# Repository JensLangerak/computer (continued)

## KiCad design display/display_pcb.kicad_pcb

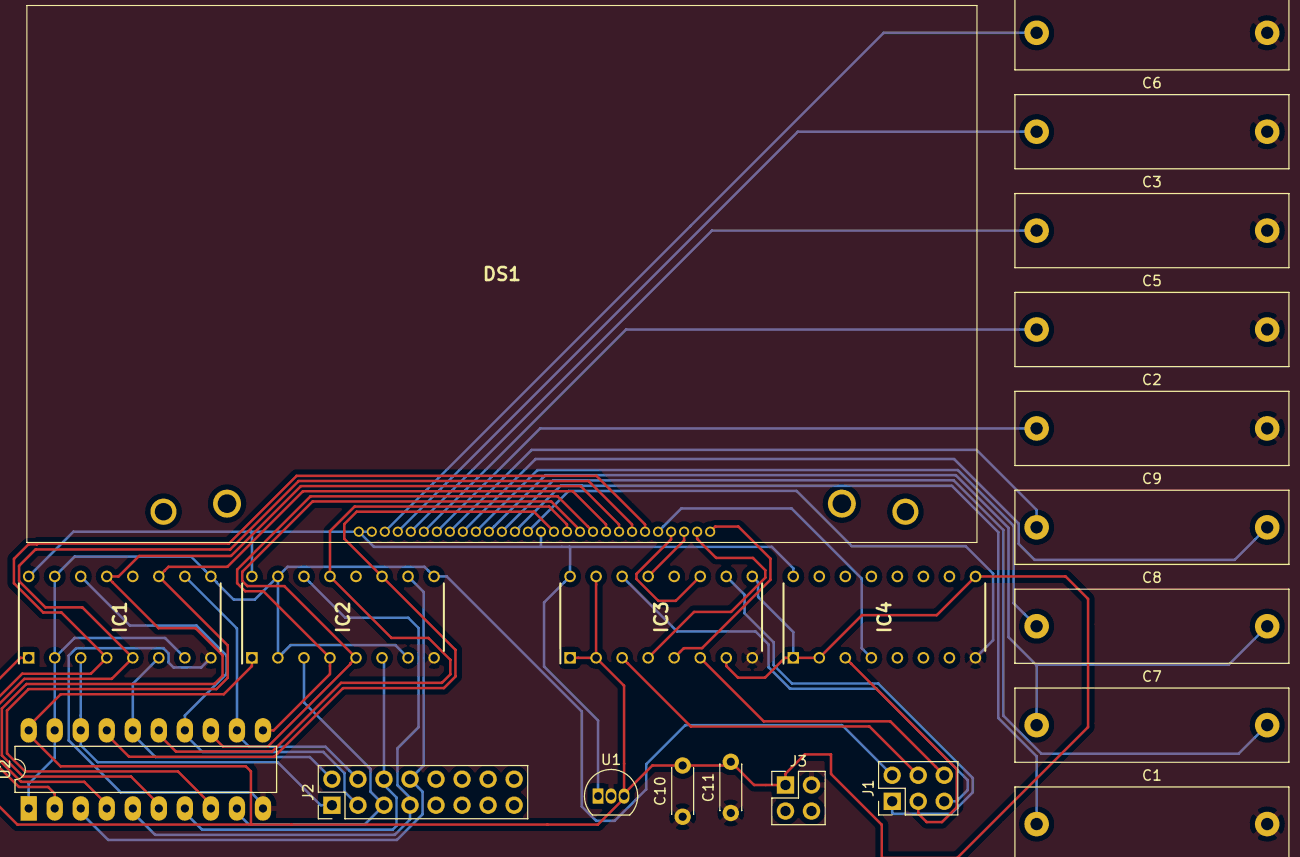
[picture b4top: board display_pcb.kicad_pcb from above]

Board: 2 copper layers, 21 parts (0 on the bottom side), 41 nets.

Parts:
C1, C2, C3, C4, C5, C6, C7, C8, C9: 1µF; C_Rect_L26.5mm_W7.0mm_P22.50mm_MKS4
C10, C11: 0.1µF; C_Disc_D4.3mm_W1.9mm_P5.00mm
DS1: NHD-C12864LZ-FSW-FBW-3V3; NHDC12864LZFSWFBW3V3
IC1, IC2, IC3, IC4: CD40109BE; DIP794W53P254L1930H508Q16N
J1: Conn_02x03_Odd_Even; PinHeader_2x03_P2.54mm_Vertical
J2: Conn_02x08_Odd_Even; PinHeader_2x08_P2.54mm_Vertical
J3: Conn_02x02_Odd_Even; PinHeader_2x02_P2.54mm_Vertical
U1: LP2950-3.0_TO92; TO-92_Inline
U2: 74LS244; DIP-20_W7.62mm_LongPads

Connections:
+3V0: DS1.14, DS1.27, DS1.28, IC1.16, IC2.16, IC3.16, IC4.16, U1.1
+5V: C10.2, C11.2, IC1.1, IC2.1, IC3.1, IC3.2, IC3.7, IC3.9, IC3.15, IC4.1, IC4.2, IC4.9, J3.1, U1.3, U2.20
/CONN BUS/D0: IC1.3, J2.1, U2.18
/CONN BUS/D1: IC1.6, J2.2, U2.16
/CONN BUS/D2: IC1.14, J2.3, U2.14
/CONN BUS/D3: IC1.10, J2.4, U2.12
/CONN BUS/D4: IC2.3, J2.5, U2.9
/CONN BUS/D5: IC2.6, J2.6, U2.7
/CONN BUS/D6: IC2.14, J2.7, U2.5
/CONN BUS/D7: IC2.10, J2.8, U2.3
/Display/A0: IC3.14, J1.5
/Display/CS: IC3.3, J1.4
/Display/DB0: DS1.6, IC1.4, U2.2
/Display/DB1: DS1.7, IC1.5, U2.4
/Display/DB2: DS1.8, IC1.13, U2.6
/Display/DB3: DS1.9, IC1.11, U2.8
/Display/DB4: DS1.10, IC2.4, U2.11
/Display/DB5: DS1.11, IC2.5, U2.13
/Display/DB6: DS1.12, IC2.13, U2.15
/Display/DB7: DS1.13, IC2.11, U2.17
/Display/DI_~DO~: IC1.2, IC1.7, IC1.9, IC1.15, IC2.2, IC2.7, IC2.9, IC2.15, J1.2, U2.1, U2.19
/Display/E: IC4.3, J1.3
/Display/RES: IC3.6, J1.6
/Display/R~W~: IC3.10, J1.1
GND: C1.2, C2.2, C3.2, C4.2, C5.2, C6.2, C10.1, C11.1, DS1.15, IC1.8, IC2.8, IC3.8, IC4.8, J3.2, U1.2, U2.10
unnamed: C1.1, DS1.16
unnamed: C2.1, DS1.22
unnamed: C3.1, DS1.24
unnamed: C4.1, DS1.26
unnamed: C5.1, DS1.23
unnamed: C6.1, DS1.25
unnamed: C7.1, C8.2, DS1.18
unnamed: C7.2, DS1.17
unnamed: C8.1, DS1.19
unnamed: C9.1, DS1.21
unnamed: C9.2, DS1.20
unnamed: DS1.1, IC3.5
unnamed: DS1.2, IC3.4
unnamed: DS1.3, IC3.13
unnamed: DS1.4, IC3.11
unnamed: DS1.5, IC4.4

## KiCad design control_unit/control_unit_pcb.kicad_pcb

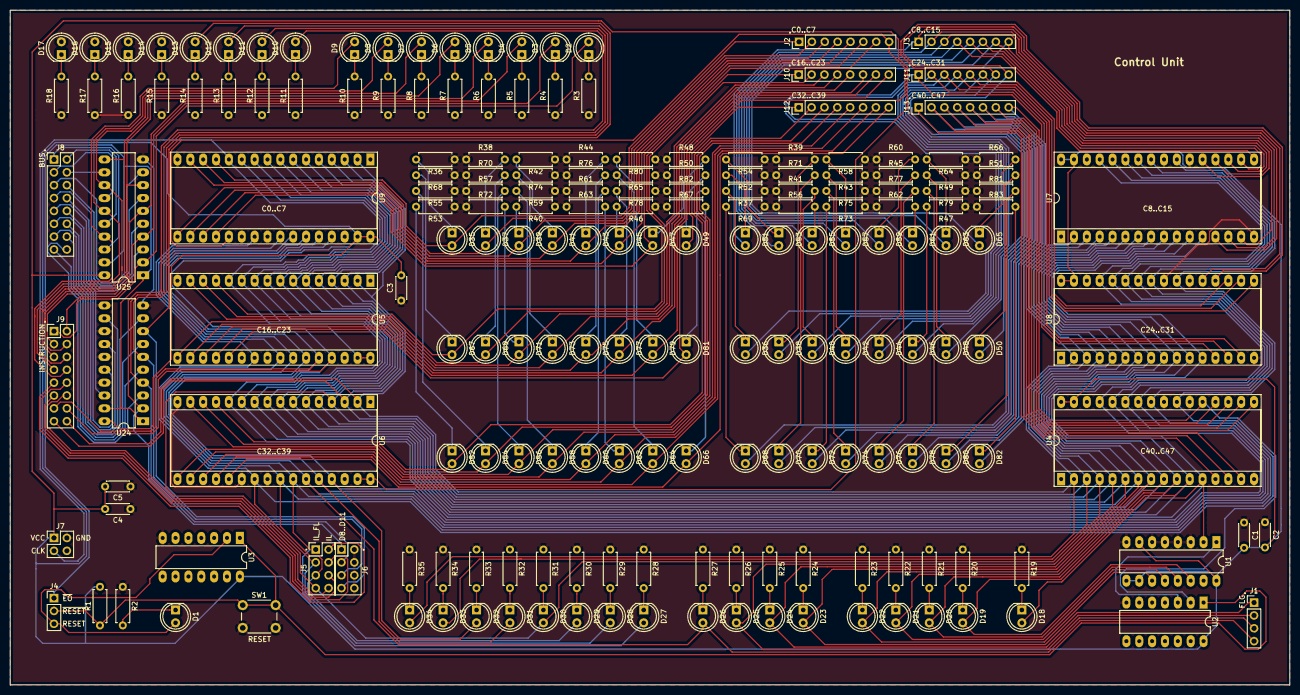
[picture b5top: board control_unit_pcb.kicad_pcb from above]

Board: 2 copper layers, 252.7 x 133.2 mm, 195 parts (0 on the bottom side), 185 nets.

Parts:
C1, C2, C3, C4, C5: 0.1µF; C_Disc_D4.3mm_W1.9mm_P5.00mm
D1, D2, D3, D4, D5, D6, D7, D8, D9, D10, D11, D12, D13, D14, D15, D16, D17, D18, D19, D20, D21, D22, D23, D24, D25, D26, D27, D28, D29, D30, D31, D32, D33, D34, D35, D36, D37, D38, D39, D40, D41, D42, D43, D44, D45, D46, D47, D48, D49, D50, D51, D52, D53, D54, D55, D56, D57, D58, D59, D60, D61, D62, D63, D64, D65, D66, D67, D68, D69, D70, D71, D72, D73, D74, D75, D76, D77, D78, D79, D80, D81, D82: LED_ALT; LED_D5.0mm
J1: Conn_01x04; PinHeader_1x04_P2.54mm_Vertical
J2, J3, J10, J11, J12, J13: Conn_01x08; PinHeader_1x08_P2.54mm_Vertical
J4: Conn_01x03; PinHeader_1x03_P2.54mm_Vertical
J5, J6: Conn_02x04_Odd_Even; PinHeader_2x04_P2.54mm_Vertical
J7: Conn_02x02_Odd_Even; PinHeader_2x02_P2.54mm_Vertical
J8, J9: Conn_02x08_Odd_Even; PinHeader_2x08_P2.54mm_Vertical
R1: 5K; R_Axial_DIN0207_L6.3mm_D2.5mm_P7.62mm_Horizontal
R2, R3, R4, R5, R6, R7, R8, R9, R10, R11, R12, R13, R14, R15, R16, R17, R18, R19, R20, R21, R22, R23, R24, R25, R26, R27, R28, R29, R30, R31, R32, R33, R34, R35, R36, R37, R38, R39, R40, R41, R42, R43, R44, R45, R46, R47, R48, R49, R50, R51, R52, R53, R54, R55, R56, R57, R58, R59, R60, R61, R62, R63, R64, R65, R66, R67, R68, R69, R70, R71, R72, R73, R74, R75, R76, R77, R78, R79, R80, R81, R82, R83: 5k; R_Axial_DIN0207_L6.3mm_D2.5mm_P7.62mm_Horizontal
SW1: SW_Push; SW_PUSH_6mm_H7.3mm
U1: 74LS163; DIP-16_W7.62mm_LongPads
U2: 74LS08; DIP-14_W7.62mm_LongPads
U3: 74LS04; DIP-14_W7.62mm_LongPads
U4, U5, U6, U7, U8, U9: SST39SF010; DIP-32_W15.24mm_Socket_LongPads
U24, U25: 74LS244; DIP-20_W7.62mm_LongPads

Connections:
/C0: D35.2, J2.1, U9.13
/C1: D37.2, J2.2, U9.14
/C2: D39.2, J2.3, U9.15
/C3: D41.2, J2.4, U9.17
/C4: D43.2, J2.5, U9.18
/C5: D45.2, J2.6, U9.19
/C6: D47.2, J2.7, U9.20
/C7: D49.2, J2.8, U9.21
/C8: D51.2, J3.1, U7.13
/C9: D53.2, J3.2, U7.14
/C10: D55.2, J3.3, U7.15
/C11: D57.2, J3.4, U7.17
/C12: D59.2, J3.5, U7.18
/C13: D61.2, J3.6, U7.19
/C14: D63.2, J3.7, U7.20
/C15: D65.2, J3.8, U7.21
/C16: D67.2, J10.1, U5.13
/C17: D69.2, J10.2, U5.14
/C18: D71.2, J10.3, U5.15
/C19: D73.2, J10.4, U5.17
/C20: D75.2, J10.5, U5.18
/C21: D77.2, J10.6, U5.19
/C22: D79.2, J10.7, U5.20
/C23: D81.2, J10.8, U5.21
/C24: D36.2, J11.1, U8.13
/C25: D38.2, J11.2, U8.14
/C26: D40.2, J11.3, U8.15
/C27: D42.2, J11.4, U8.17
/C28: D44.2, J11.5, U8.18
/C29: D46.2, J11.6, U8.19
/C30: D48.2, J11.7, U8.20
/C31: D50.2, J11.8, U8.21
/C32: D52.2, J12.1, U6.13
/C33: D54.2, J12.2, U6.14
/C34: D56.2, J12.3, U6.15
/C35: D58.2, J12.4, U6.17
/C36: D60.2, J12.5, U6.18
/C37: D62.2, J12.6, U6.19
/C38: D64.2, J12.7, U6.20
/C39: D66.2, J12.8, U6.21
/C40: D68.2, J13.1, U4.13
/C41: D70.2, J13.2, U4.14
/C42: D72.2, J13.3, U4.15
/C43: D74.2, J13.4, U4.17
/C44: D76.2, J13.5, U4.18
/C45: D78.2, J13.6, U4.19
/C46: D80.2, J13.7, U4.20
/C47: D82.2, J13.8, U2.2, U4.21
/D_8: D10.2, J6.1, U24.2
/D_9: D11.2, J6.3, U24.4
/D_10: D12.2, J6.5, U24.6
/D_11: D13.2, J6.7, U24.8
/FLG0: D23.2, J1.1, U4.7, U5.7, U6.7, U7.7, U8.7, U9.7
/FLG1: D24.2, J1.2, U4.6, U5.6, U6.6, U7.6, U8.6, U9.6
/FLG2: D25.2, J1.3, U4.5, U5.5, U6.5, U7.5, U8.5, U9.5
/FLG3: D26.2, J1.4, U4.27, U5.27, U6.27, U7.27, U8.27, U9.27
/IL_0: J5.2, J9.9
/IL_1: J5.4, J9.10
/IL_2: J5.6, J9.11
/IL_3: J5.8, J9.12
/IL_FL_0: D27.2, J5.1, U4.26, U5.26, U6.26, U7.26, U8.26, U9.26
/IL_FL_1: D28.2, J5.3, U4.23, U5.23, U6.23, U7.23, U8.23, U9.23
/IL_FL_2: D29.2, J5.5, U4.25, U5.25, U6.25, U7.25, U8.25, U9.25
/IL_FL_3: D30.2, J5.7, U4.4, U5.4, U6.4, U7.4, U8.4, U9.4
/bus/D0: J8.1, U25.18
/bus/D1: J8.2, U25.16
/bus/D2: J8.3, U25.14
/bus/D3: J8.4, U25.12
/bus/D4: J8.5, U25.9
/bus/D5: J8.6, U25.7
/bus/D6: J8.7, U25.5
/bus/D7: J8.8, U25.3
/bus/D8: J8.9, U24.18
/bus/D9: J8.10, U24.16
/bus/D10: J8.11, U24.14
/bus/D11: J8.12, U24.12
/bus/D12: J8.13, U24.9
/bus/D13: J8.14, U24.7
/bus/D14: J8.15, U24.5
/bus/D15: J8.16, U24.3
/control unit/A1: D19.2, U1.14, U4.11, U5.11, U6.11, U7.11, U8.11, U9.11
/control unit/A2: D20.2, U1.13, U4.10, U5.10, U6.10, U7.10, U8.10, U9.10
/control unit/A3: D21.2, U1.12, U4.9, U5.9, U6.9, U7.9, U8.9, U9.9
/control unit/A4: D22.2, U1.11, U4.8, U5.8, U6.8, U7.8, U8.8, U9.8
/control unit/A13: D31.2, J9.13, U4.28, U5.28, U6.28, U7.28, U8.28, U9.28
/control unit/A14: D32.2, J9.14, U4.29, U5.29, U6.29, U7.29, U8.29, U9.29
/control unit/A15: D33.2, J9.15, U4.3, U5.3, U6.3, U7.3, U8.3, U9.3
/control unit/A16: D34.2, J9.16, U4.2, U5.2, U6.2, U7.2, U8.2, U9.2
/control unit/CLK: D18.2, J7.3, U1.2, U4.12, U5.12, U6.12, U7.12, U8.12, U9.12
/control unit/RESET: D1.2, J4.3, U3.2
/control unit/~EO~: J4.1, U24.1, U24.19, U25.1, U25.19
/control unit/~RC~: U1.1, U2.3
/control unit/~RESET~: J4.2, R1.1, SW1.1, U2.1, U3.1
/instruction/D0: D2.2, J9.1, U25.2
/instruction/D1: D3.2, J9.2, U25.4
/instruction/D2: D4.2, J9.3, U25.6
/instruction/D3: D5.2, J9.4, U25.8
/instruction/D4: D6.2, J9.5, U25.11
/instruction/D5: D7.2, J9.6, U25.13
/instruction/D6: D8.2, J9.7, U25.15
/instruction/D7: D9.2, J9.8, U25.17
GND: C1.1, C2.1, C3.1, C4.1, C5.1, D14.2, D15.2, D16.2, D17.2, J6.2, J6.4, J6.6, J6.8, J7.2, R2.1, R3.1, R4.1, R5.1, R6.1, R7.1, R8.1, R9.1, R10.1, R11.1, R12.1, R13.1, R14.1, R15.1, R16.1, R17.1, R18.1, R19.1, R20.1, R21.1, R22.1, R23.1, R24.1, R25.1, R26.1, R27.1, R28.1, R29.1, R30.1, R31.1, R32.1, R33.1, R34.1, R35.1, R36.1, R37.1, R38.1, R39.1, R40.1, R41.1, R42.1, R43.1, R44.1, R45.1, R46.1, R47.1, R48.1, R49.1, R50.1, R51.1, R52.1, R53.1, R54.1, R55.1, R56.1, R57.1, R58.1, R59.1, R60.1, R61.1, R62.1, R63.1, R64.1, R65.1, R66.1, R67.1, R68.1, R69.1, R70.1, R71.1, R72.1, R73.1, R74.1, R75.1, R76.1, R77.1, R78.1, R79.1, R80.1, R81.1, R82.1, R83.1, SW1.2, U1.3, U1.4, U1.5, U1.6, U1.8, U2.7, U3.7, U4.16, U4.22, U4.24, U5.16, U5.22, U5.24, U6.16, U6.22, U6.24, U7.16, U7.22, U7.24, U8.16, U8.22, U8.24, U9.16, U9.22, U9.24, U24.10, U24.11, U24.13, U24.15, U24.17, U25.10
unnamed: D1.1, R2.2
unnamed: D2.1, R3.2
unnamed: D3.1, R4.2
unnamed: D4.1, R5.2
unnamed: D5.1, R6.2
unnamed: D6.1, R7.2
unnamed: D7.1, R8.2
unnamed: D8.1, R9.2
unnamed: D9.1, R10.2
unnamed: D10.1, R11.2
unnamed: D11.1, R12.2
unnamed: D12.1, R13.2
unnamed: D13.1, R14.2
unnamed: D14.1, R15.2
unnamed: D15.1, R16.2
unnamed: D16.1, R17.2
unnamed: D17.1, R18.2
unnamed: D18.1, R19.2
unnamed: D19.1, R20.2
unnamed: D20.1, R21.2
unnamed: D21.1, R22.2
unnamed: D22.1, R23.2
unnamed: D23.1, R24.2
unnamed: D24.1, R25.2
unnamed: D25.1, R26.2
unnamed: D26.1, R27.2
unnamed: D27.1, R28.2
unnamed: D28.1, R29.2
unnamed: D29.1, R30.2
unnamed: D30.1, R31.2
unnamed: D31.1, R32.2
unnamed: D32.1, R33.2
unnamed: D33.1, R34.2
unnamed: D34.1, R35.2
unnamed: D35.1, R36.2
unnamed: D36.1, R37.2
unnamed: D37.1, R38.2
unnamed: D38.1, R39.2
unnamed: D39.1, R40.2
unnamed: D40.1, R41.2
unnamed: D41.1, R42.2
unnamed: D42.1, R43.2
unnamed: D43.1, R44.2
unnamed: D44.1, R45.2
unnamed: D45.1, R46.2
unnamed: D46.1, R47.2
unnamed: D47.1, R48.2
unnamed: D48.1, R49.2
unnamed: D49.1, R50.2
unnamed: D50.1, R51.2
unnamed: D51.1, R52.2
unnamed: D52.1, R53.2
unnamed: D53.1, R54.2
unnamed: D54.1, R55.2
unnamed: D55.1, R56.2
unnamed: D56.1, R57.2
unnamed: D57.1, R58.2
unnamed: D58.1, R59.2
unnamed: D59.1, R60.2
unnamed: D60.1, R61.2
unnamed: D61.1, R62.2
unnamed: D62.1, R63.2
unnamed: D63.1, R64.2
unnamed: D64.1, R65.2
unnamed: D65.1, R66.2
unnamed: D66.1, R67.2
unnamed: D67.1, R68.2
unnamed: D68.1, R69.2
unnamed: D69.1, R70.2
unnamed: D70.1, R71.2
unnamed: D71.1, R72.2
unnamed: D72.1, R73.2
unnamed: D73.1, R74.2
unnamed: D74.1, R75.2
unnamed: D75.1, R76.2
unnamed: D76.1, R77.2
unnamed: D77.1, R78.2
unnamed: D78.1, R79.2
unnamed: D79.1, R80.2
unnamed: D80.1, R81.2
unnamed: D81.1, R82.2
unnamed: D82.1, R83.2
VCC: C1.2, C2.2, C3.2, C4.2, C5.2, J7.1, R1.2, U1.7, U1.9, U1.10, U1.16, U2.14, U3.14, U4.31, U4.32, U5.31, U5.32, U6.31, U6.32, U7.31, U7.32, U8.31, U8.32, U9.31, U9.32, U24.20, U25.20

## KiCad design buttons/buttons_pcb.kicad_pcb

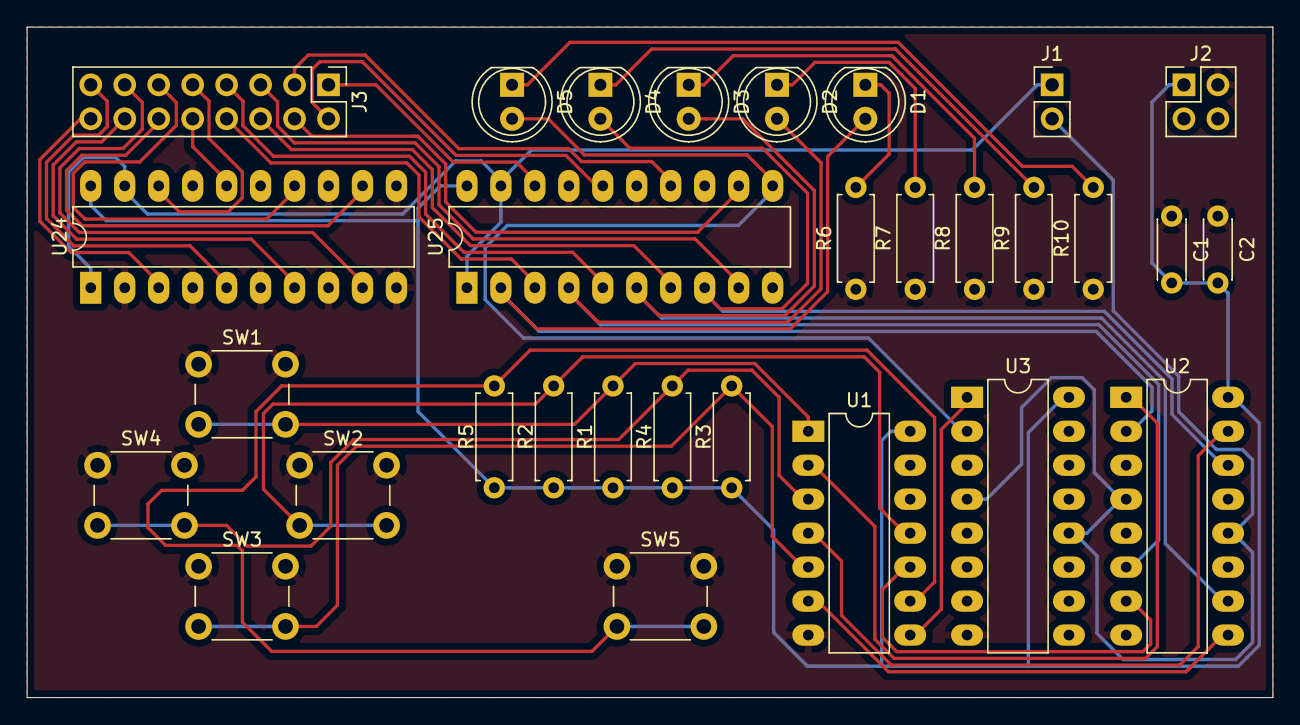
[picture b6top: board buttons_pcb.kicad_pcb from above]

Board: 2 copper layers, 93.2 x 50.1 mm, 30 parts (0 on the bottom side), 40 nets.

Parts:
C1, C2: 0.1µF; C_Disc_D4.3mm_W1.9mm_P5.00mm
D1, D2, D3, D4, D5: LED_ALT; LED_D5.0mm
J1: Conn_01x02; PinHeader_1x02_P2.54mm_Vertical
J2: Conn_02x02_Odd_Even; PinHeader_2x02_P2.54mm_Vertical
J3: Conn_02x08_Odd_Even; PinHeader_2x08_P2.54mm_Vertical
R1, R2, R3, R4, R5, R6, R7, R8, R9, R10: 5k; R_Axial_DIN0207_L6.3mm_D2.5mm_P7.62mm_Horizontal
SW1, SW2, SW3, SW4, SW5: SW_Push; SW_PUSH_6mm_H7.3mm
U1: 74LS04; DIP-14_W7.62mm_LongPads
U2, U3: 74LS375; DIP-16_W7.62mm_LongPads
U24, U25: 74LS244; DIP-20_W7.62mm_LongPads

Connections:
/BUTTONS/Clear: J1.2, U2.4, U2.12, U3.4, U3.12
/BUTTONS/D0: D1.2, U2.2, U25.2
/BUTTONS/D1: D2.2, U2.6, U25.4
/BUTTONS/D2: D3.2, U2.10, U25.6
/BUTTONS/D3: D4.2, U2.14, U25.8
/BUTTONS/D4: D5.2, U3.2, U25.11
/BUTTONS/~EO~: J1.1, U24.1, U24.19, U25.1, U25.19
/CONN BUS/D0: J3.1, U25.18
/CONN BUS/D1: J3.2, U25.16
/CONN BUS/D2: J3.3, U25.14
/CONN BUS/D3: J3.4, U25.12
/CONN BUS/D4: J3.5, U25.9
/CONN BUS/D5: J3.6, U25.7
/CONN BUS/D6: J3.7, U25.5
/CONN BUS/D7: J3.8, U25.3
/CONN BUS/D8: J3.9, U24.18
/CONN BUS/D9: J3.10, U24.16
/CONN BUS/D10: J3.11, U24.14
/CONN BUS/D11: J3.12, U24.12
/CONN BUS/D12: J3.13, U24.9
/CONN BUS/D13: J3.14, U24.7
/CONN BUS/D14: J3.15, U24.5
/CONN BUS/D15: J3.16, U24.3
GND: C1.1, C2.1, J2.2, R6.1, R7.1, R8.1, R9.1, R10.1, SW1.1, SW2.1, SW3.1, SW4.1, SW5.1, U1.7, U2.8, U3.8, U24.2, U24.4, U24.6, U24.8, U24.10, U24.11, U24.13, U24.15, U24.17, U25.10, U25.13, U25.15, U25.17
unnamed: D1.1, R6.2
unnamed: D2.1, R7.2
unnamed: D3.1, R8.2
unnamed: D4.1, R9.2
unnamed: D5.1, R10.2
unnamed: R1.2, SW1.2, U1.1
unnamed: R2.2, SW2.2, U1.11
unnamed: R3.2, SW3.2, U1.5
unnamed: R4.2, SW4.2, U1.3
unnamed: R5.2, SW5.2, U1.9
unnamed: U1.2, U2.1
unnamed: U1.4, U2.15
unnamed: U1.6, U2.9
unnamed: U1.8, U3.1
unnamed: U1.10, U2.7
VCC: C1.2, C2.2, J2.1, R1.1, R2.1, R3.1, R4.1, R5.1, U1.14, U2.16, U3.16, U24.20, U25.20

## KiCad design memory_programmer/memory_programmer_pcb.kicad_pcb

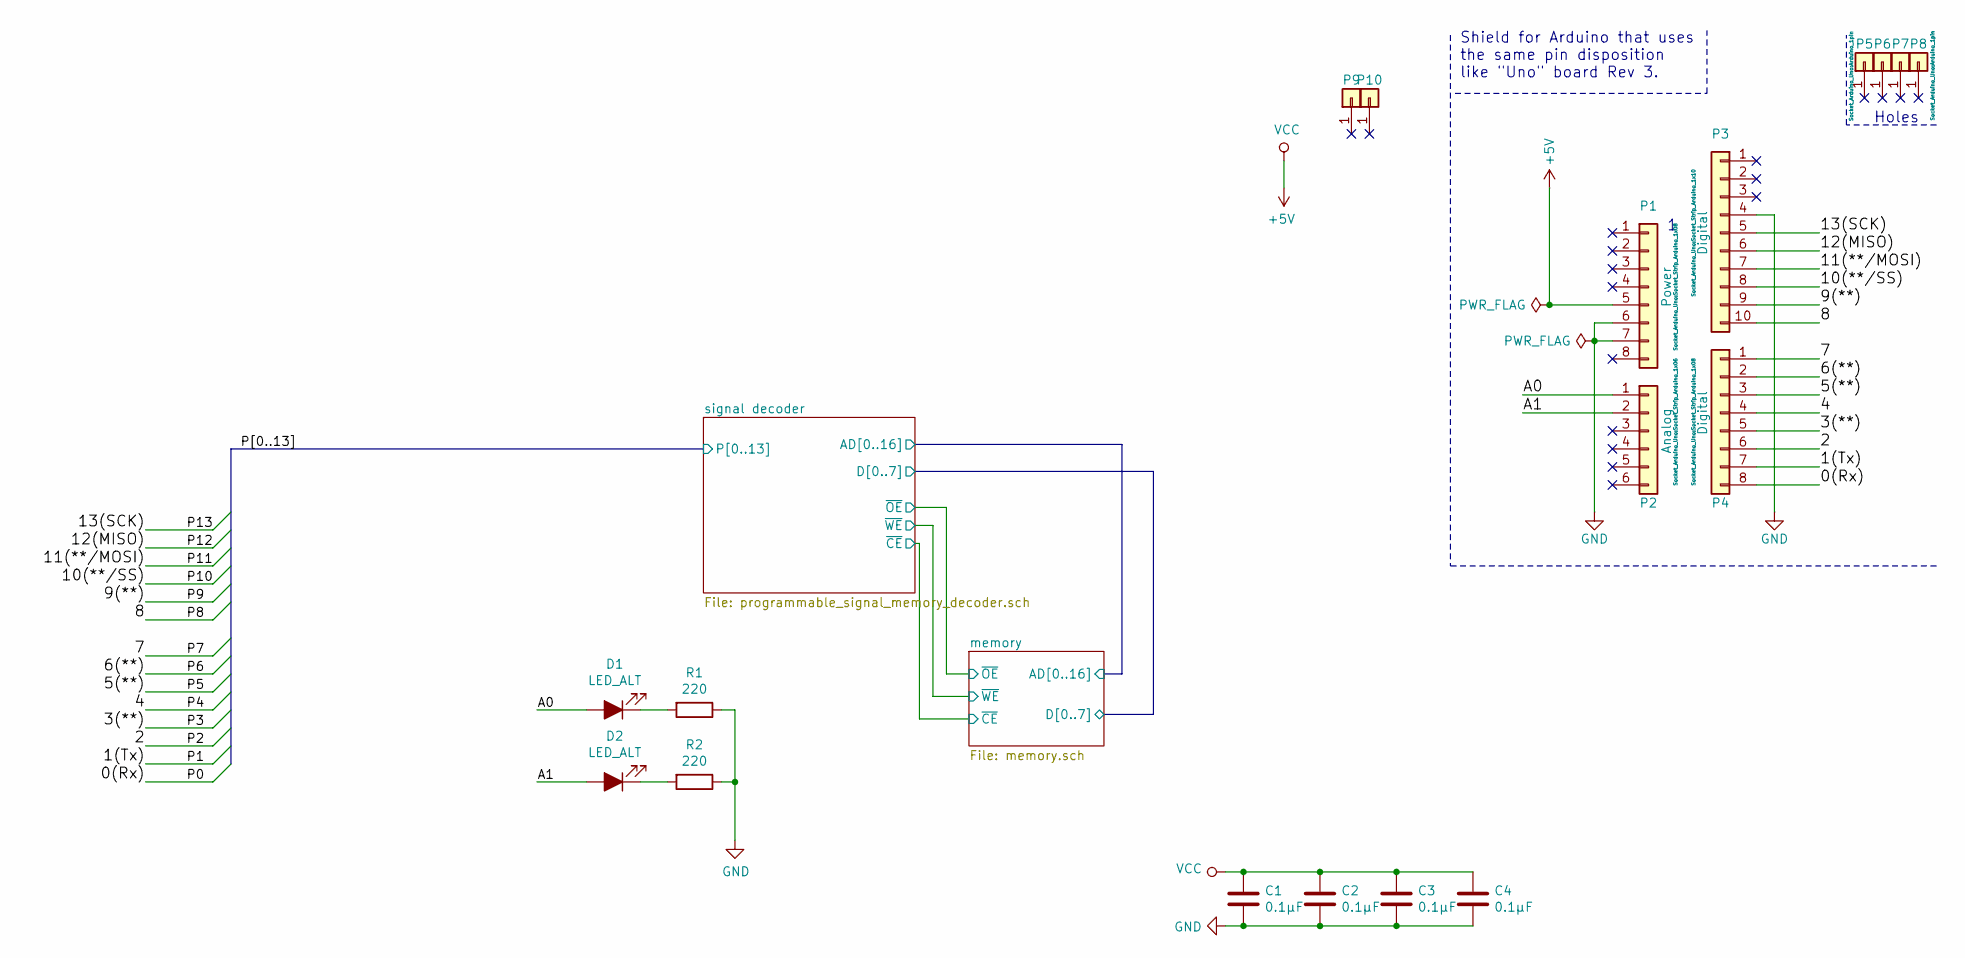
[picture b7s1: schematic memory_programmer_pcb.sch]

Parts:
C1, C2, C3, C4: 0.1µF; C_Disc_D4.3mm_W1.9mm_P5.00mm
D1, D2: LED_ALT; LED_D5.0mm
P1: Power; Socket_Strip_Arduino_1x08
P2: Analog; Socket_Strip_Arduino_1x06
P3: Digital; Socket_Strip_Arduino_1x10
P4: Digital; Socket_Strip_Arduino_1x08
P5, P6, P7, P8, P9, P10: CONN_01X01; Arduino_1pin
R1, R2: 220; R_Axial_DIN0207_L6.3mm_D2.5mm_P7.62mm_Horizontal

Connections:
+5V: C1.2, C2.2, C3.2, C4.2, P1.5; also elsewhere on the board
/0(Rx): P4.8; also elsewhere on the board
/1(Tx): P4.7; also elsewhere on the board
/2: P4.6; also elsewhere on the board
/3(**): P4.5; also elsewhere on the board
/4: P4.4; also elsewhere on the board
/5(**): P4.3; also elsewhere on the board
/6(**): P4.2; also elsewhere on the board
/7: P4.1; also elsewhere on the board
/8: P3.10; also elsewhere on the board
/9(**): P3.9; also elsewhere on the board
/10(**/SS): P3.8; also elsewhere on the board
/11(**/MOSI): P3.7; also elsewhere on the board
/12(MISO): P3.6; also elsewhere on the board
/13(SCK): P3.5; also elsewhere on the board
/A0: D1.2 (A), P2.1
/A1: D2.2 (A), P2.2
GND: C1.1, C2.1, C3.1, C4.1, P1.6, P1.7, P3.4, R1.1, R2.1; also elsewhere on the board
unnamed: D1.1 (K), R1.2
unnamed: D2.1 (K), R2.2

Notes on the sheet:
Holes
Shield for Arduino that uses the same pin disposition like "Uno" board Rev 3.

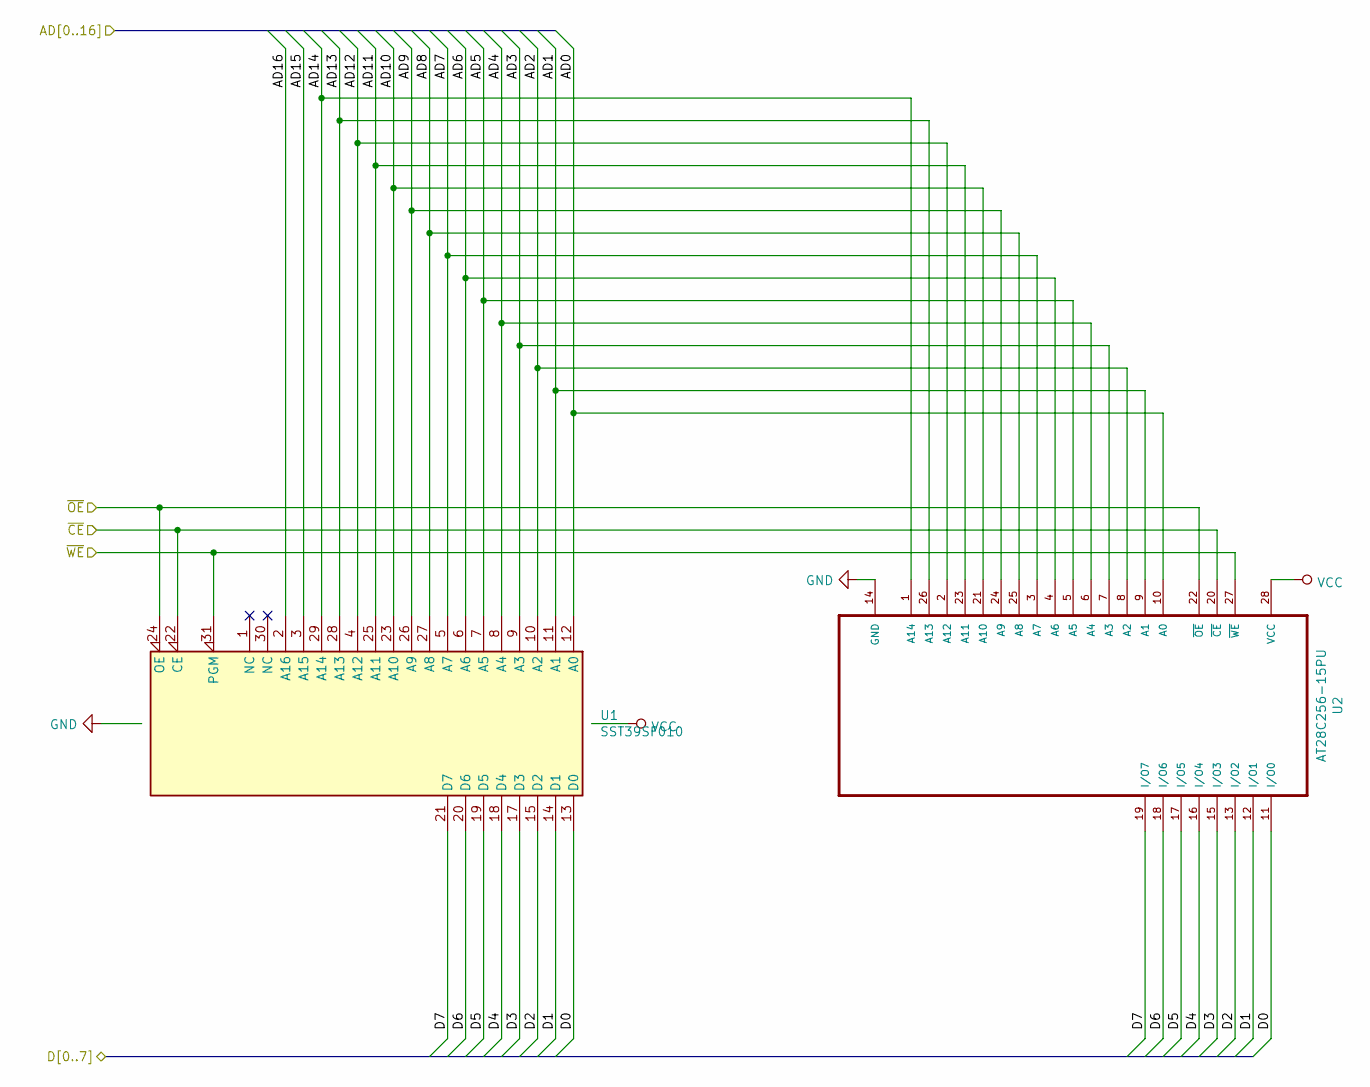
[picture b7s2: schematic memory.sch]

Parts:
U1: SST39SF010; DIP-32_W15.24mm_Socket_LongPads
U2: AT28C256-15PU; DIP-28_W15.24mm_Socket_LongPads

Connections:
+5V: U1.32 (VCC), U2.28 (VCC); also elsewhere on the board
/10(**/SS): U1.22 (CE), U2.20 (~CE); also elsewhere on the board
/11(**/MOSI): U1.31 (PGM), U2.27 (~WE); also elsewhere on the board
/12(MISO): U1.24 (OE), U2.22 (~OE); also elsewhere on the board
/memory/AD0: U1.12 (A0), U2.10 (A0); also elsewhere on the board
/memory/AD1: U1.11 (A1), U2.9 (A1); also elsewhere on the board
/memory/AD2: U1.10 (A2), U2.8 (A2); also elsewhere on the board
/memory/AD3: U1.9 (A3), U2.7 (A3); also elsewhere on the board
/memory/AD4: U1.8 (A4), U2.6 (A4); also elsewhere on the board
/memory/AD5: U1.7 (A5), U2.5 (A5); also elsewhere on the board
/memory/AD6: U1.6 (A6), U2.4 (A6); also elsewhere on the board
/memory/AD7: U1.5 (A7), U2.3 (A7); also elsewhere on the board
/memory/AD8: U1.27 (A8), U2.25 (A8); also elsewhere on the board
/memory/AD9: U1.26 (A9), U2.24 (A9); also elsewhere on the board
/memory/AD10: U1.23 (A10), U2.21 (A10); also elsewhere on the board
/memory/AD11: U1.25 (A11), U2.23 (A11); also elsewhere on the board
/memory/AD12: U1.4 (A12), U2.2 (A12); also elsewhere on the board
/memory/AD13: U1.28 (A13), U2.26 (A13); also elsewhere on the board
/memory/AD14: U1.29 (A14), U2.1 (A14); also elsewhere on the board
/memory/AD15: U1.3 (A15); also elsewhere on the board
/memory/AD16: U1.2 (A16); also elsewhere on the board
/memory/D0: U1.13 (D0), U2.11 (I/O0); also elsewhere on the board
/memory/D1: U1.14 (D1), U2.12 (I/O1); also elsewhere on the board
/memory/D2: U1.15 (D2), U2.13 (I/O2); also elsewhere on the board
/memory/D3: U1.17 (D3), U2.15 (I/O3); also elsewhere on the board
/memory/D4: U1.18 (D4), U2.16 (I/O4); also elsewhere on the board
/memory/D5: U1.19 (D5), U2.17 (I/O5); also elsewhere on the board
/memory/D6: U1.20 (D6), U2.18 (I/O6); also elsewhere on the board
/memory/D7: U1.21 (D7), U2.19 (I/O7); also elsewhere on the board
GND: U1.16 (GND), U2.14 (GND); also elsewhere on the board

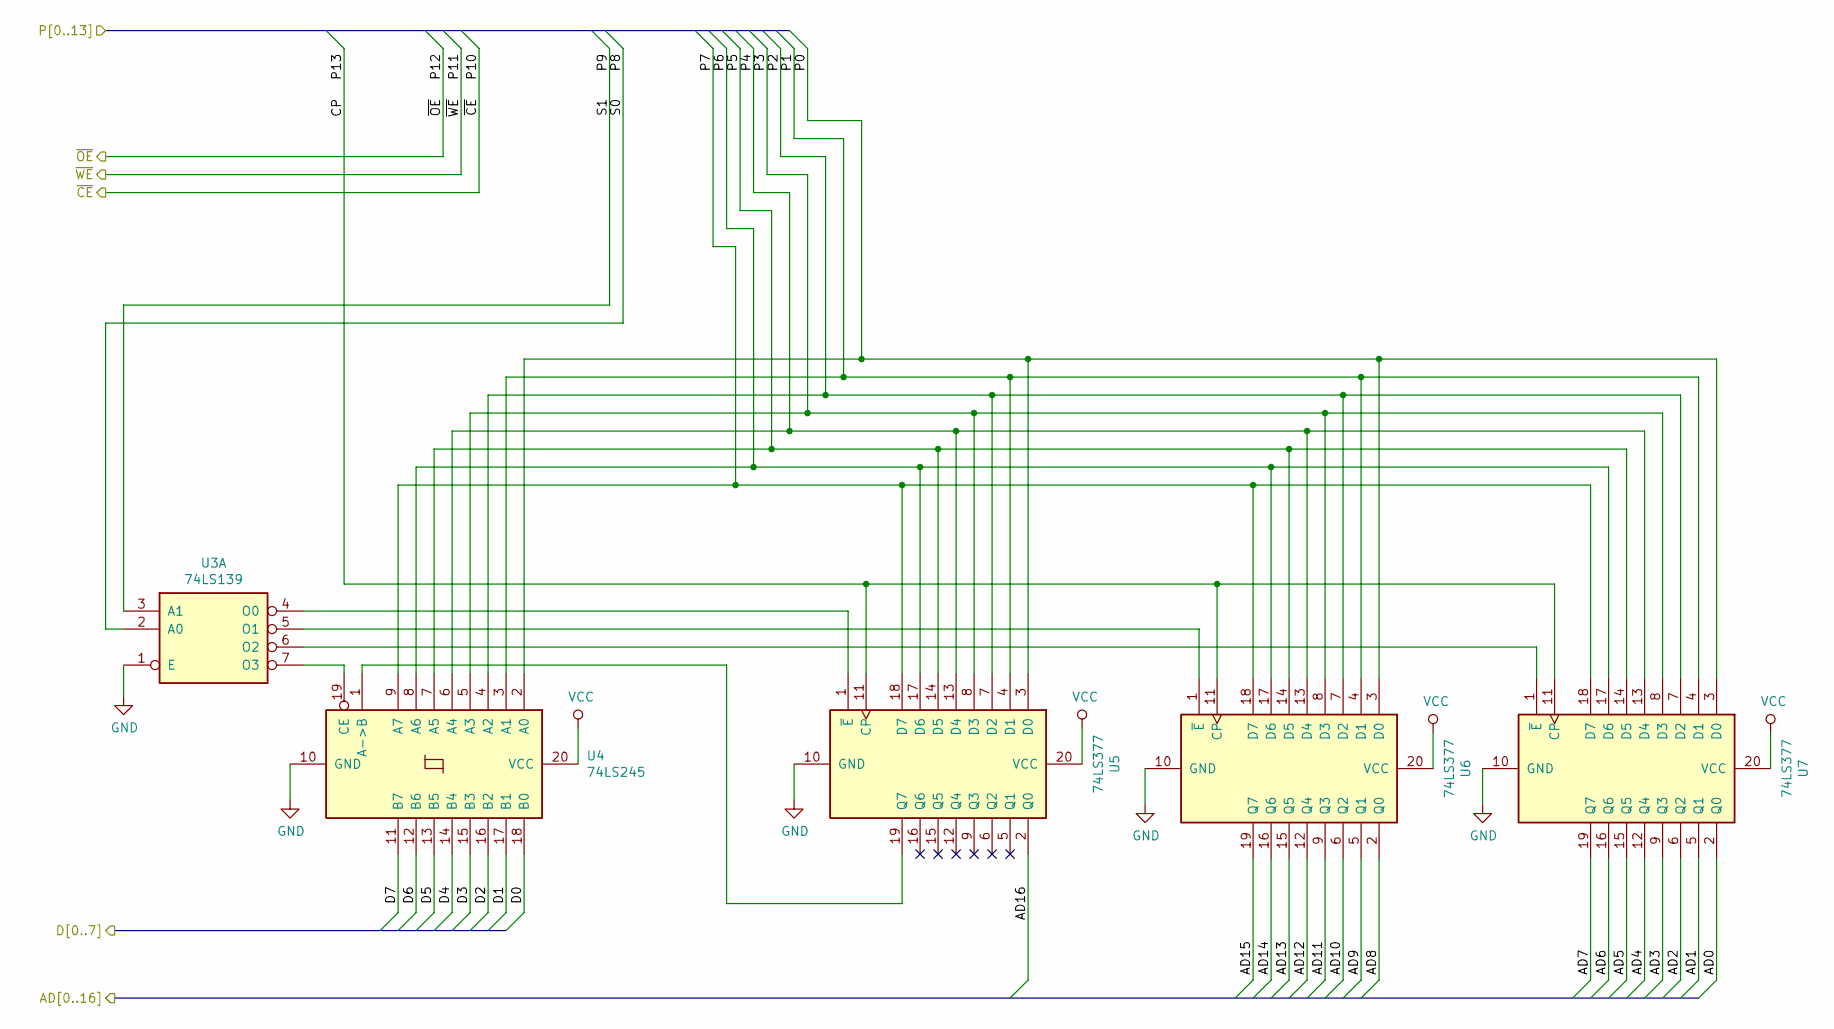
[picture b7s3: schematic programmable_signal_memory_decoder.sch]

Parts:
U3: 74LS139; DIP-16_W7.62mm_LongPads
U4: 74LS245; DIP-20_W7.62mm_LongPads
U5, U6, U7: 74LS377; DIP-20_W7.62mm_LongPads

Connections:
+5V: U4.20 (VCC), U5.20 (VCC), U6.20 (VCC), U7.20 (VCC); also elsewhere on the board
/0(Rx): U4.2 (A0), U5.3 (D0), U6.3 (D0), U7.3 (D0); also elsewhere on the board
/1(Tx): U4.3 (A1), U5.4 (D1), U6.4 (D1), U7.4 (D1); also elsewhere on the board
/2: U4.4 (A2), U5.7 (D2), U6.7 (D2), U7.7 (D2); also elsewhere on the board
/3(**): U4.5 (A3), U5.8 (D3), U6.8 (D3), U7.8 (D3); also elsewhere on the board
/4: U4.6 (A4), U5.13 (D4), U6.13 (D4), U7.13 (D4); also elsewhere on the board
/5(**): U4.7 (A5), U5.14 (D5), U6.14 (D5), U7.14 (D5); also elsewhere on the board
/6(**): U4.8 (A6), U5.17 (D6), U6.17 (D6), U7.17 (D6); also elsewhere on the board
/7: U4.9 (A7), U5.18 (D7), U6.18 (D7), U7.18 (D7); also elsewhere on the board
/8: U3.2 (A0); also elsewhere on the board
/9(**): U3.3 (A1); also elsewhere on the board
/13(SCK): U5.11 (CP), U6.11 (CP), U7.11 (CP); also elsewhere on the board
/memory/AD0: U7.2 (Q0); also elsewhere on the board
/memory/AD1: U7.5 (Q1); also elsewhere on the board
/memory/AD2: U7.6 (Q2); also elsewhere on the board
/memory/AD3: U7.9 (Q3); also elsewhere on the board
/memory/AD4: U7.12 (Q4); also elsewhere on the board
/memory/AD5: U7.15 (Q5); also elsewhere on the board
/memory/AD6: U7.16 (Q6); also elsewhere on the board
/memory/AD7: U7.19 (Q7); also elsewhere on the board
/memory/AD8: U6.2 (Q0); also elsewhere on the board
/memory/AD9: U6.5 (Q1); also elsewhere on the board
/memory/AD10: U6.6 (Q2); also elsewhere on the board
/memory/AD11: U6.9 (Q3); also elsewhere on the board
/memory/AD12: U6.12 (Q4); also elsewhere on the board
/memory/AD13: U6.15 (Q5); also elsewhere on the board
/memory/AD14: U6.16 (Q6); also elsewhere on the board
/memory/AD15: U6.19 (Q7); also elsewhere on the board
/memory/AD16: U5.2 (Q0); also elsewhere on the board
/memory/D0: U4.18 (B0); also elsewhere on the board
/memory/D1: U4.17 (B1); also elsewhere on the board
/memory/D2: U4.16 (B2); also elsewhere on the board
/memory/D3: U4.15 (B3); also elsewhere on the board
/memory/D4: U4.14 (B4); also elsewhere on the board
/memory/D5: U4.13 (B5); also elsewhere on the board
/memory/D6: U4.12 (B6); also elsewhere on the board
/memory/D7: U4.11 (B7); also elsewhere on the board
GND: U3.1 (E), U4.10 (GND), U5.10 (GND), U6.10 (GND), U7.10 (GND); also elsewhere on the board
unnamed: U3.4 (O0), U5.1 (~E)
unnamed: U3.5 (O1), U6.1 (~E)
unnamed: U3.6 (O2), U7.1 (~E)
unnamed: U3.7 (O3), U4.19 (CE)
unnamed: U4.1 (A->B), U5.19 (Q7)

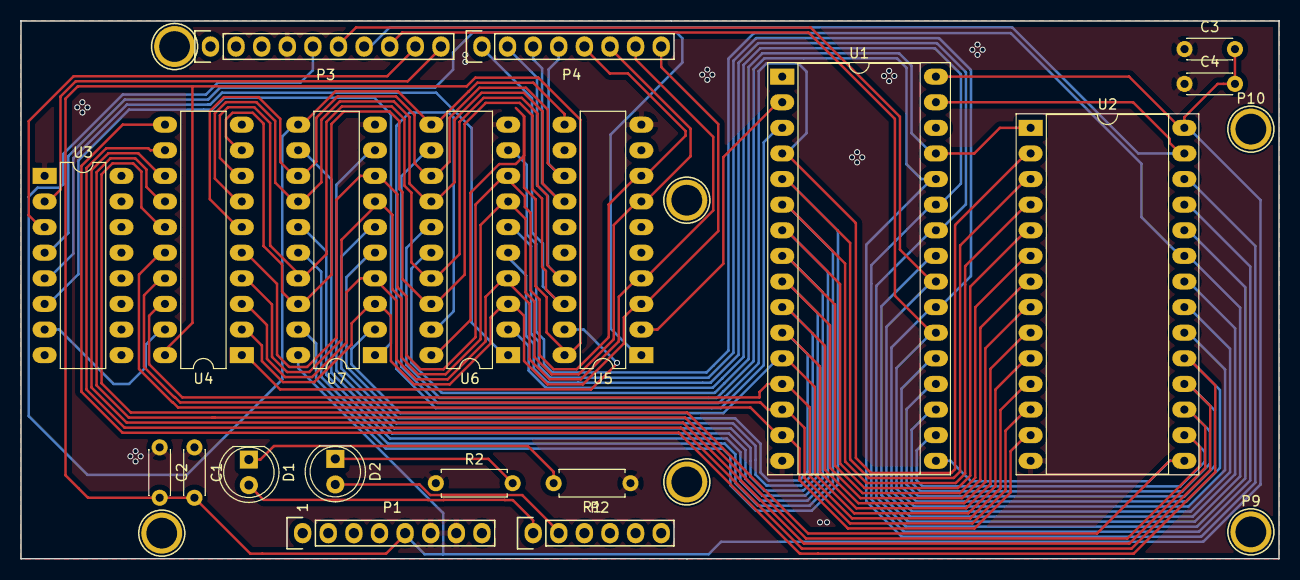
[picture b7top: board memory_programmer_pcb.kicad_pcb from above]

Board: 2 copper layers, 124.8 x 53.3 mm, 25 parts (0 on the bottom side), 50 nets.
